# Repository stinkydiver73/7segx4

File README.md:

7segx4
======

big seven segment display

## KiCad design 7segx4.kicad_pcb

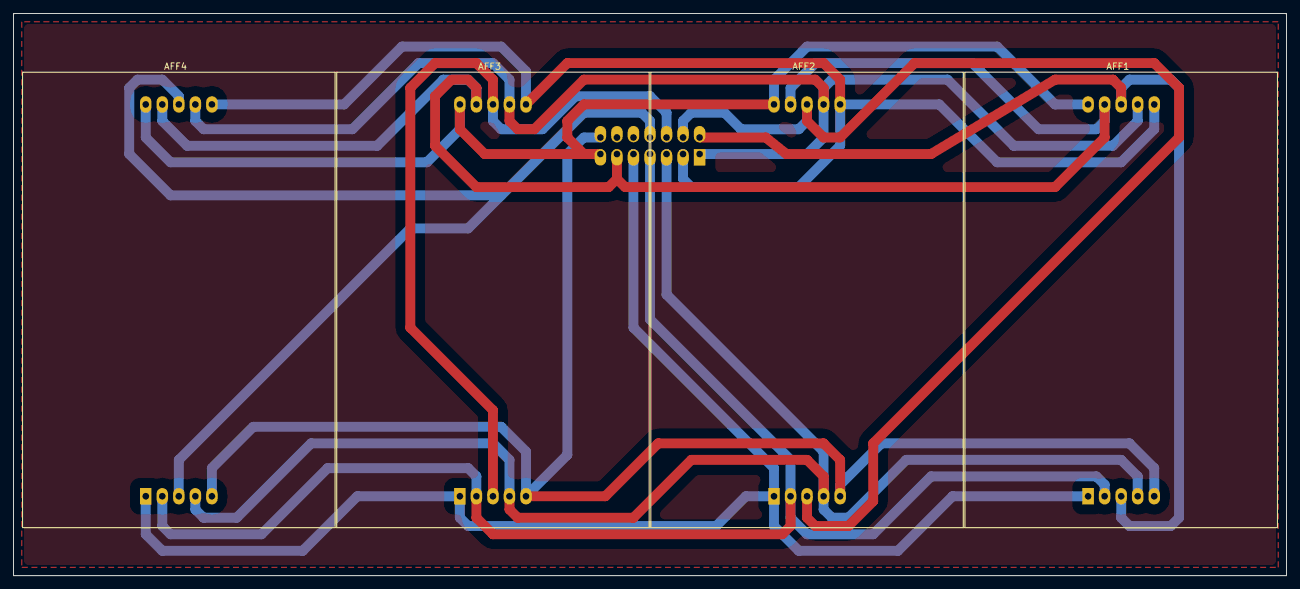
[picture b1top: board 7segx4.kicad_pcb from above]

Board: 2 copper layers, 195.6 x 86.4 mm, 5 parts (1 on the bottom side), 12 nets.

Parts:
AFF1, AFF2, AFF3, AFF4: 7SEGMENTLED; sc23-kingbright
x1: HEADER2X7; header2x7

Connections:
/a: AFF1.7, AFF2.7, AFF3.7, AFF4.7, x1.1
/b: AFF1.6, AFF2.6, AFF3.6, AFF4.6, x1.3
/bank1: AFF1.3, AFF1.8, x1.2
/bank2: AFF2.3, AFF2.8, x1.4
/bank3: AFF3.3, AFF3.8, x1.6
/bank4: AFF4.3, AFF4.8, x1.8
/c: AFF1.4, AFF2.4, AFF3.4, AFF4.4, x1.5
/d: AFF1.2, AFF2.2, AFF3.2, AFF4.2, x1.7
/e: AFF1.1, AFF2.1, AFF3.1, AFF4.1, x1.9
/f: AFF1.9, AFF2.9, AFF3.9, AFF4.9, x1.11
/g: AFF1.10, AFF2.10, AFF3.10, AFF4.10, x1.13
/p: AFF1.5, AFF2.5, AFF3.5, AFF4.5, x1.14

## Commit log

2014-03-11 connector moved
2014-03-12 nem jo a luk
2014-03-12 1 juk atirva
2014-03-25 track width+
2014-04-16 size changes
2014-04-16 size changed
